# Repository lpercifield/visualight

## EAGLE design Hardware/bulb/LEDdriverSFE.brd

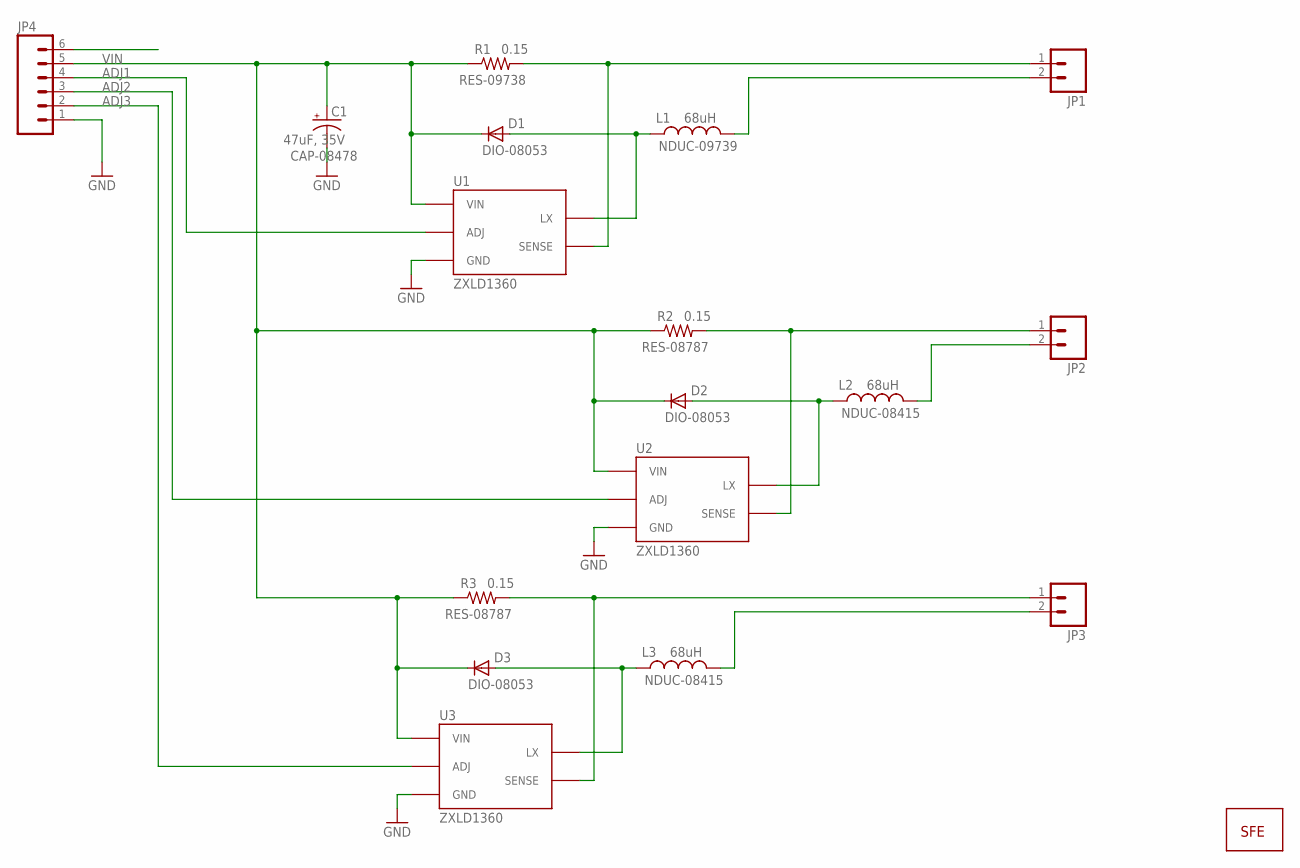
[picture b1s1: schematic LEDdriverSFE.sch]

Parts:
C1: 47uF, 35V; PANASONIC_D
D1, D2, D3: MBRA140; SMA-DIODE
JP1, JP2, JP3: M02; 1X02_LONGPADS
JP4: M06SIP; 1X06
JP5: LOGO-SFENEW; SFE-NEW-WEBLOGO
L1, L2, L3: 68uH; CR75
R1, R2, R3: 0.15; 0603-RES
U1, U2, U3: ZXLD1360; SOT23-5

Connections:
ADJ1: JP4.4, U1.3 (ADJ)
ADJ2: JP4.3, U2.3 (ADJ)
ADJ3: JP4.2, U3.3 (ADJ)
GND: C1.-, JP4.1, U1.2 (GND), U2.2 (GND), U3.2 (GND)
unnamed: JP1.2, L1.P$2 (2)
unnamed: D2.A, L2.P$1 (1), U2.1 (LX)
unnamed: JP2.1, R2.2, U2.4 (SENSE)
unnamed: D1.A, L1.P$1 (1), U1.1 (LX)
unnamed: JP1.1, R1.2, U1.4 (SENSE)
unnamed: JP2.2, L2.P$2 (2)
unnamed: D3.A, L3.P$1 (1), U3.1 (LX)
unnamed: JP3.1, R3.2, U3.4 (SENSE)
unnamed: JP3.2, L3.P$2 (2)
VIN: C1.+, D1.C, D2.C, D3.C, JP4.5, R1.1, R2.1, R3.1, U1.5 (VIN), U2.5 (VIN), U3.5 (VIN)

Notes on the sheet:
NDUC-09739
RES-09738
CAP-08478
DIO-08053
NDUC-08415
RES-08787

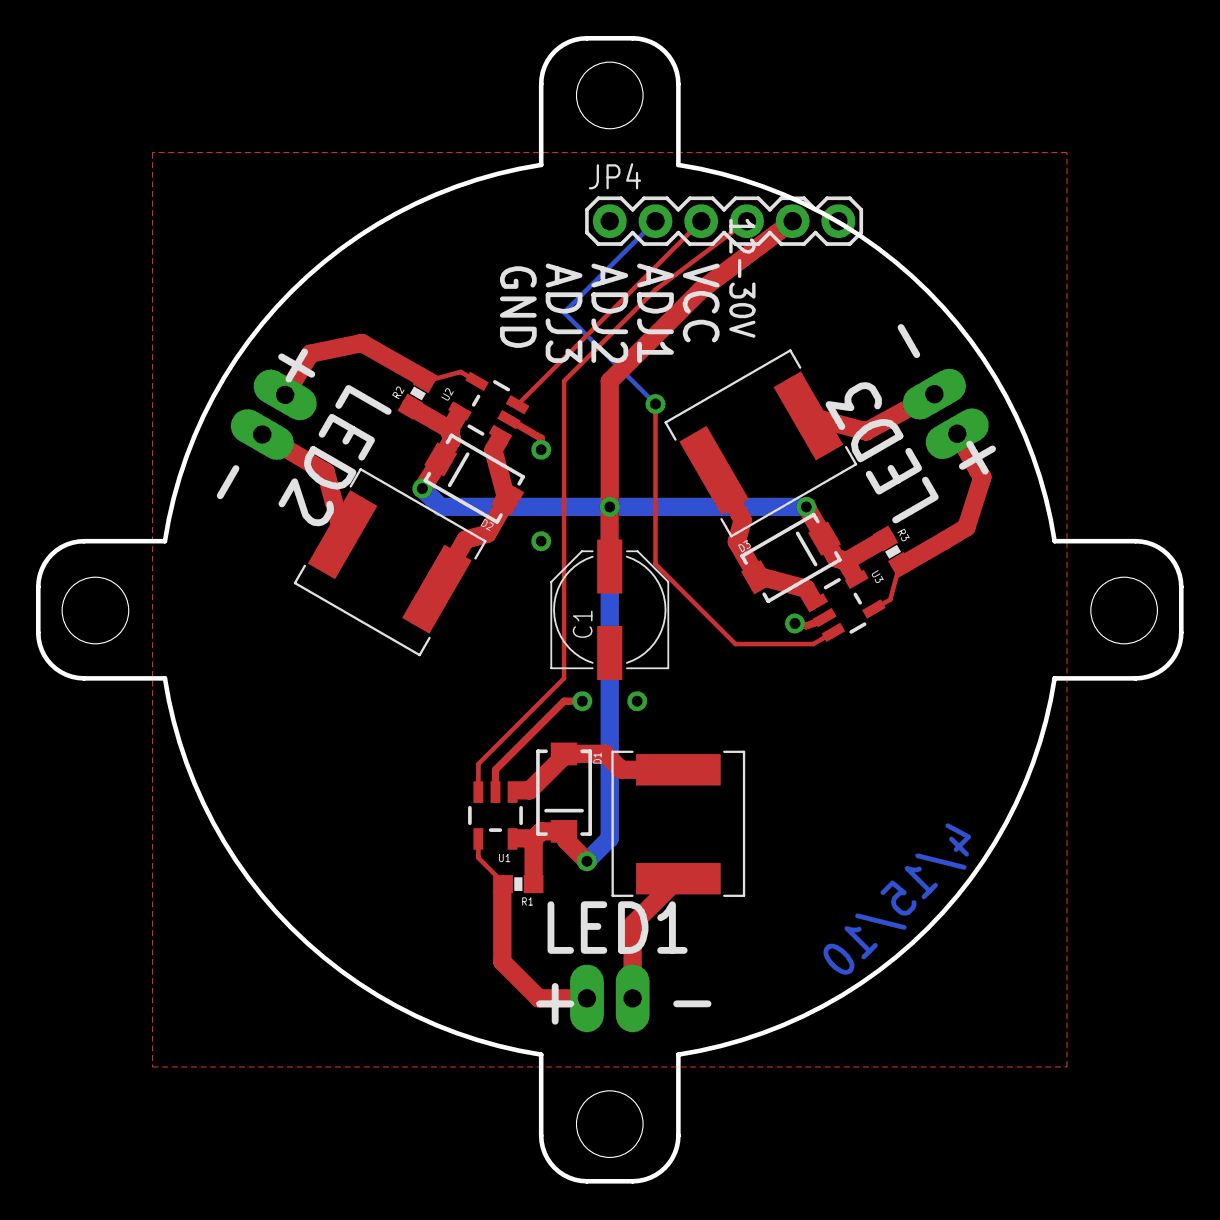
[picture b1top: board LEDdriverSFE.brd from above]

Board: 2 copper layers, 63.5 x 63.5 mm, 18 parts (1 on the bottom side), 14 nets.

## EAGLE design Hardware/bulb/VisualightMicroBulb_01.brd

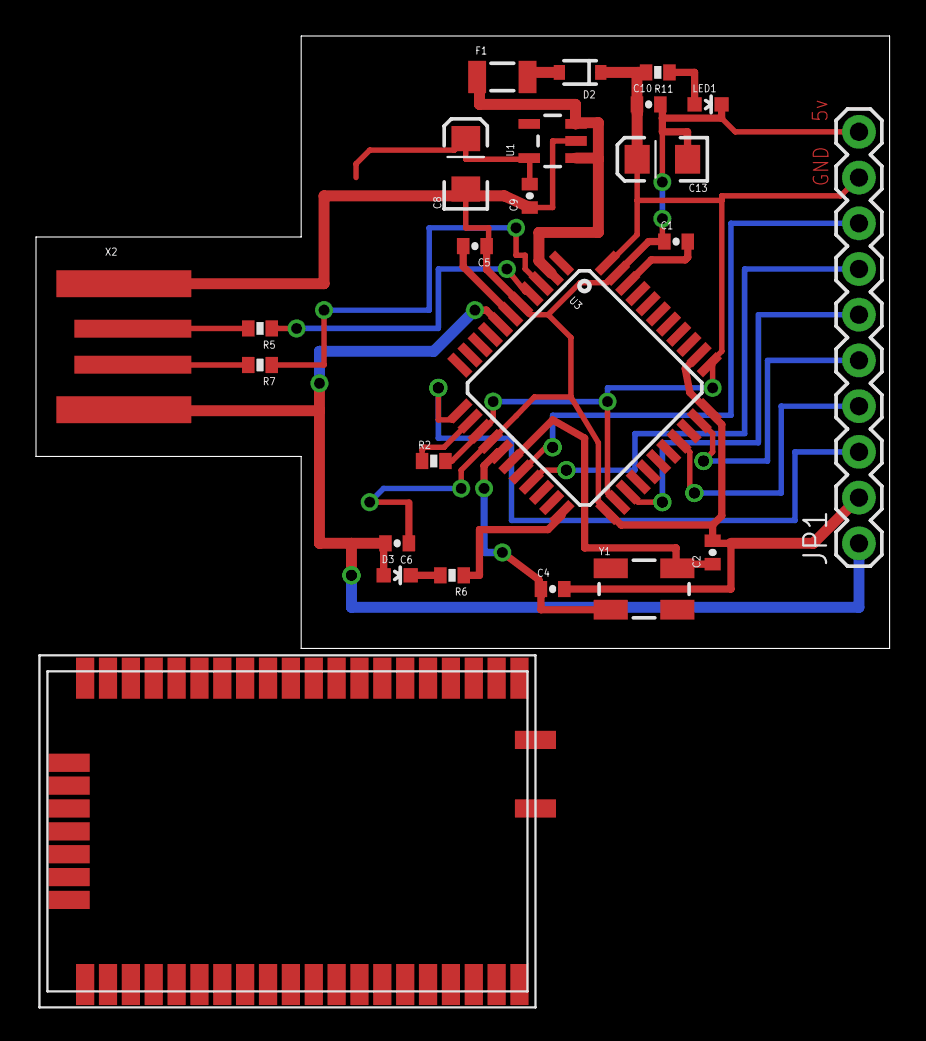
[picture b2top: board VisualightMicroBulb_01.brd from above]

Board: 2 copper layers, 47.4 x 34.0 mm, 24 parts (0 on the bottom side), 23 nets.

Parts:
C1, C9: 0.1uF; 0402-CAP
C2, C4: 22pF; 0402-CAP
C5, C6, C10: 1uF; 0402-CAP
C8, C13: 10uF; EIA3216
D2: SOD-323
D3: Green; LED-0603
F1: 500mA; PTC-1206
JP1: M10"; 1X10
LED1: Red; LED-0603
R2: 10K; 0402-RES
R5, R7: 22; 0402-RES
R6: 330; 0402-RES
R11: 1K; 0402-RES
U1: MIC5219 3.3V; SOT23-5
U3: ATMEGA32U4; SPARKFUN-DIGITALIC_TQFP44
X1: RN-171
X2: USBPCB; USB-A-PCB
Y1: 16MHz; CRYSTAL-SMD-5X3

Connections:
+3V3_OUT: C8.A, C9.2, U1.5, X1.10, X1.34, X1.49
AREF: C1.2, U3.42
D2: JP1.7, U3.19
D3: JP1.8, U3.18
D4: JP1.6, U3.25
D10: JP1.4, U3.30
D11: JP1.3, U3.12
D13: JP1.5, U3.32
D+: R5.1, U3.4
D-: R7.1, U3.3
GND: C1.1, C2.2, C4.2, C5.1, C6.1, C8.C, C9.1, C10.2, C13.C, JP1.2, JP1.10, LED1.C, U1.2, U3.5, U3.15, U3.23, U3.33, U3.35, U3.43, X1.1, X1.14, X1.20, X1.21, X1.22, X1.23, X1.25, X1.26, X1.39, X2.GND
unnamed: C4.1, U3.16, Y1.1
unnamed: C2.1, U3.17, Y1.3
unnamed: C5.2, U3.6
unnamed: R7.2, X2.USB_M
unnamed: D3.C, R6.2
unnamed: R5.2, X2.USB_P
unnamed: D2.2, F1.2
unnamed: LED1.A, R11.1
RESET: R2.1, U3.13
TXLED: R6.1, U3.22
UVCC: C6.2, D3.A, F1.1, JP1.1, U1.1, U1.3, U3.2, U3.7, X2.5V
VCC: C10.1, C13.A, D2.1, JP1.9, R2.2, R11.2, U3.14, U3.24, U3.34, U3.44

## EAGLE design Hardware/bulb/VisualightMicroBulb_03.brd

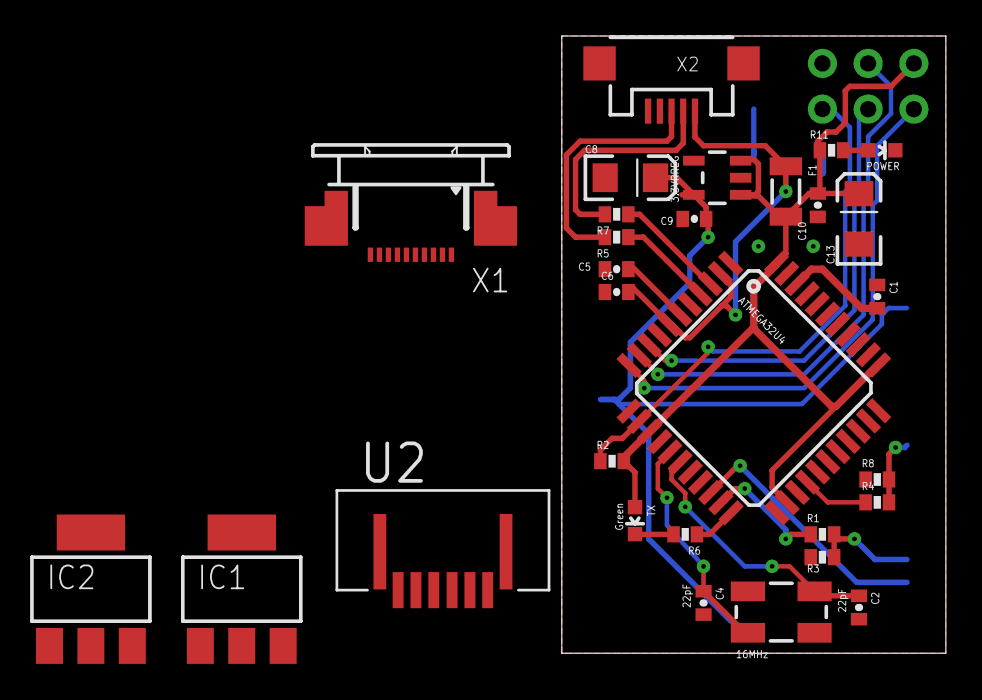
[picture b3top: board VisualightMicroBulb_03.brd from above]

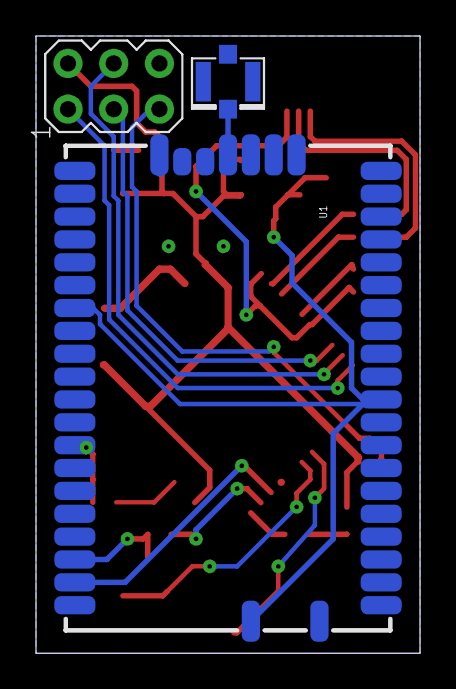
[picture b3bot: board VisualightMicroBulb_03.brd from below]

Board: 2 copper layers, 21.3 x 34.3 mm, 32 parts (3 on the bottom side), 29 nets.

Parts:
3.3VRREG: MIC5219 3.3V; SOT23-5
ATMEGA32U4: ATMEGA32U4; SPARKFUN-DIGITALIC_TQFP44
C1, C9: 0.1uF; 0402-CAP
C2, C4: 22pF; 0402-CAP
C5, C6, C10: 1uF; 0402-CAP
C8, C13: 10uF; EIA3216
F1: 500mA; PTC-1206
IC1, IC2: LD117AS25TR; SOT223
ISP1: AVRISP-6; AVRISP
POWER: Red; LED-0603
R1, R4: 2.2K; 0402-RES
R2: 10K; 0402-RES
R3, R8: 3.3K; 0402-RES
R5, R7: 22; 0402-RES
R6: 330; 0402-RES
R11: 1K; 0402-RES
TX: Green; LED-0603
U1: RN171RN171; RN171
U2: SFW6R-3STE1LF; FCI_SFW6R-3STE1LF
U$1: U.FL
X1: 52745-1090
X2: USB-MICROB
Y1: 16MHz; CRYSTAL-SMD-5X3

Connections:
+3V3_OUT: 3.3VRREG.5, C8.A, C9.2, U1.10, U1.34, U1.49
ANT: U1.24, U$1.P$3
AREF: ATMEGA32U4.42, C1.2
D5: ATMEGA32U4.31, U2.4, X1.4
D9: ATMEGA32U4.29, U2.3, X1.3
D10: ATMEGA32U4.30, U2.2, X1.2
D12: ATMEGA32U4.26, R4.1
D13: ATMEGA32U4.32, U2.1, X1.1
D+: ATMEGA32U4.4, R5.1, X1.5
D-: ATMEGA32U4.3, R7.1, X1.6
GND: 3.3VRREG.2, ATMEGA32U4.5, ATMEGA32U4.15, ATMEGA32U4.23, ATMEGA32U4.33, ATMEGA32U4.35, ATMEGA32U4.43, C1.1, C2.2, C4.2, C5.1, C6.1, C8.C, C9.1, C10.2, C13.C, ISP1.6, POWER.C, R3.1, R8.1, U1.21, U1.22, U1.23, U1.25, U1.26, U1.27, U2.5, U$1.P$1, U$1.P$2, X1.9, X1.10, X2.GND, X2.MT1, X2.MT2
MISO: ATMEGA32U4.11, ISP1.1
MOSI: ATMEGA32U4.10, ISP1.4
unnamed: ATMEGA32U4.16, C4.1, Y1.1
unnamed: ATMEGA32U4.17, C2.1, Y1.3
unnamed: ATMEGA32U4.6, C5.2
unnamed: R7.2, X2.D-
unnamed: R6.2, TX.C
unnamed: R5.2, X2.D+
unnamed: POWER.A, R11.1
RESET: ATMEGA32U4.13, ISP1.5, R2.1
SCK: ATMEGA32U4.9, ISP1.3
TX: ATMEGA32U4.21, R1.1
TXLED: ATMEGA32U4.22, R6.1
UVCC: ATMEGA32U4.2, ATMEGA32U4.7, C6.2, F1.1, X1.8, X2.VBUS
VCC: 3.3VRREG.1, 3.3VRREG.3, ATMEGA32U4.14, ATMEGA32U4.24, ATMEGA32U4.34, ATMEGA32U4.44, C10.1, C13.A, F1.2, ISP1.2, R2.2, R11.2, TX.A
WIFIDIN: R1.2, R3.2, U1.45
WIFIDOUT: ATMEGA32U4.20, U1.46
WIFIRESET: R4.2, R8.2, U1.40

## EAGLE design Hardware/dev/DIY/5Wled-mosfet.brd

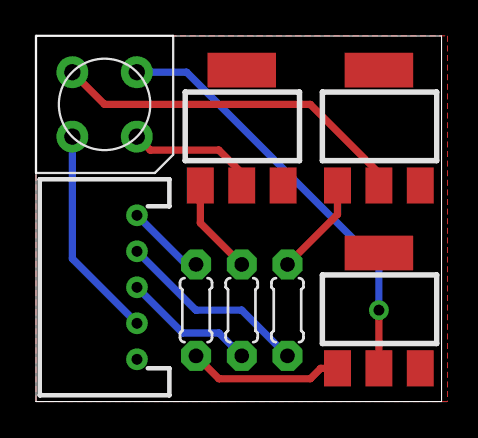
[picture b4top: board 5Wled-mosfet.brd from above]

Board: 2 copper layers, 22.5 x 20.3 mm, 8 parts (0 on the bottom side), 11 nets.

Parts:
LED1: RGBLED_CA4.5MM; 5WRGBLED
PL1: DF3R-05
Q1, Q2, Q3: IRLL024; SOT-223
R1, R2, R3: 0204/5

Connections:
BLUE: Q1.1, R1.2
GND: PL1.5, Q1.3, Q2.3, Q3.3
GREEN: Q3.1, R3.2
unnamed: LED1.1, Q1.2
unnamed: LED1.3, Q3.2
unnamed: LED1.2, Q2.2
unnamed: PL1.1, R2.1
unnamed: PL1.2, R3.1
unnamed: PL1.3, R1.1
RED: Q2.1, R2.2
VCC: LED1.4, PL1.4

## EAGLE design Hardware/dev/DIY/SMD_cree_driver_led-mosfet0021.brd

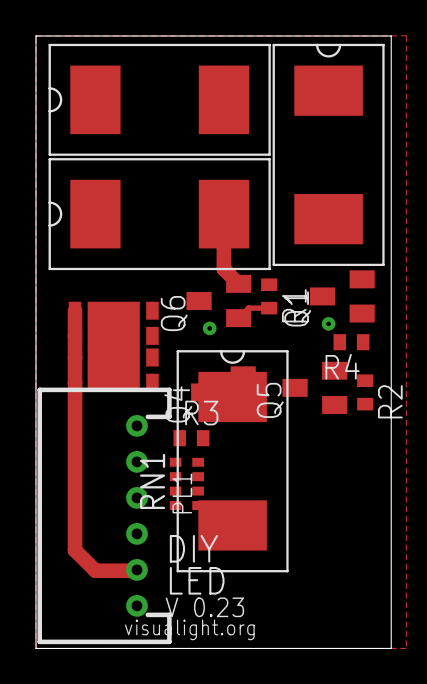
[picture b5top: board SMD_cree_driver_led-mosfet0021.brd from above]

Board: 2 copper layers, 19.7 x 34.0 mm, 15 parts (0 on the bottom side), 18 nets.

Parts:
PL1: DF3R-06
Q1, Q4, Q5, Q6: BSS123; SOT23
R1, R2, R3, R4: 100k; R0402
RN1: 0603-ARC
U$1: CREE_XLAMP_RGBW; CREE_XLAMP_XML
U$2, U$3, U$4, U$5: NSI50350AST3G; SMC-2

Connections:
BLUE: Q4.1, R3.2, RN1.7
BLUE_OUT: PL1.4, RN1.4
GND: PL1.6, R1.1, R2.1, R3.1, R4.1, U$2.C, U$3.C, U$4.C, U$5.C
GREEN: Q6.1, R1.2, RN1.6
GREEN_OUT: PL1.2, RN1.2
unnamed: Q6.3, U$1.6
unnamed: Q5.3, U$1.7
unnamed: Q4.3, U$1.8
unnamed: Q6.2, U$2.A
unnamed: PL1.1, RN1.1
unnamed: Q4.2, U$4.A
unnamed: Q5.2, U$3.A
unnamed: Q1.2, U$5.A
unnamed: Q1.3, U$1.5
RED: Q5.1, R2.2, RN1.5
RED_OUT: PL1.3, RN1.3
VCC: PL1.5, U$1.1, U$1.2, U$1.3, U$1.4
WHITE: Q1.1, R4.2, RN1.8

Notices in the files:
parts and their libraries:
SparkFun-Connectors: Licensing: CC v3.0 Share-Alike You are welcome to use this library for commercial purposes.
